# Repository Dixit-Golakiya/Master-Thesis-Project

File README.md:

# Microcontroller-Based Health Monitoring System for Supercapacitors

**Master's Thesis — Hochschule Bremen, Department of Electronics Engineering**
In cooperation with BLOCK Transformatoren-Elektronik GmbH

| | |
|---|---|
| **Author** | Golakiya Dixit |
| **Date** | 06.05.2026 |
| **Examiners** | Prof. Dr.-Ing. Dennis Kampen, Prof. Dr.-Ing. Friedrich Fleischmann |
| **Supervisor** | Dipl.-Ing. Henning Sauerland |

📄 Full thesis report: [`docs/Master_Thesis_5274929_Dixit_Golakiya.pdf`](docs/Master_Thesis_5274929_Dixit_Golakiya.pdf)

---

## Table of Contents

- [Abstract](#abstract)
- [Gallery](#gallery)
- [System Overview](#system-overview)
- [Repository Structure](#repository-structure)
- [Hardware Summary](#hardware-summary)
- [Firmware Summary](#firmware-summary)
- [Build / Open Instructions](#build--open-instructions)
- [Results Snapshot](#results-snapshot)
- [License](#license)
- [Citation](#citation)

---

## Abstract

Supercapacitors are increasingly used in energy storage applications due to their
high power density, rapid charge–discharge capability, and long cycle life. Their
performance degrades over time through capacitance fade and rising equivalent
series resistance (ESR), so monitoring state of health (SoH) is essential for
system efficiency, reliability, and safety.

This project implements a microcontroller-based health monitoring system on an
STM32G474RE platform. The system measures voltage and current during
galvanostatic charge/discharge cycles to estimate per-cell capacitance and ESR
in real time — with no external lab instrumentation. ESR is extracted from the
instantaneous ohmic voltage drop at discharge start, and capacitance from a
least-squares linear regression over the discharge slope. Both run entirely on
the MCU after each discharge cycle, with results reported over UART.

The system was validated on a 40-cell (5 parallel × 8 series) Vishay 25 F
supercapacitor bank, including artificially aged cells (accelerated thermal
ageing), across eleven test configurations. Aged cells were correctly localised
in every tested configuration, with capacitance drops of 10.9–16.5% in
single-string tests and a practical detection floor of ~10% per-cell loss in a
four-string parallel bank.

---

## Gallery

<table>
<tr>
<td width="50%">

<p align="center"><sub><b>Assembled board — isometric view</b></sub></p>
</td>
<td width="50%">

<p align="center"><sub><b>Assembled board — alternate angle</b></sub></p>
</td>
</tr>
<tr>
<td width="50%">

<p align="center"><sub><b>PCB 3D render — top</b></sub></p>
</td>
<td width="50%">

<p align="center"><sub><b>PCB 3D render — bottom</b></sub></p>
</td>
</tr>
<tr>
<td width="50%">

<p align="center"><sub><b>Galvanostatic discharge waveform</b></sub></p>
</td>
<td width="50%">

<p align="center"><sub><b>Least-squares capacitance regression</b></sub></p>
</td>
</tr>
<tr>
<td width="50%">

<p align="center"><sub><b>Power density comparison</b></sub></p>
</td>
<td width="50%">

<p align="center"><sub><b>LTspice discharge model simulation</b></sub></p>
</td>
</tr>
</table>

Higher-resolution schematic renders (front/back copper) are also available as PDFs in
[`Figure/`](Figure/): [`A_Super_Capacitor_measurement.pdf`](Figure/A_Super_Capacitor_measurement.pdf),
[`B_1_Super_Capacitor_measurement-F_Cu.pdf`](Figure/B_1_Super_Capacitor_measurement-F_Cu.pdf),
[`B_2_Super_Capacitor_measurement-B_Cu.pdf`](Figure/B_2_Super_Capacitor_measurement-B_Cu.pdf).

---

## System Overview

```
STM32G4 Nucleo-64 Board
   ├── Voltage Divider Network                  → 8 series-cell node voltages → ADC
   ├── Shunt Current Sensors (INA241A1 × 2)      → analog input
   ├── Hall-Effect Sensor (TMCS1108A3)           → analog input, isolated
   ├── MOSFET Current Sink (IRL540N / FQA140N10) → DAC/PWM controlled
   ├── Threshold Comparators (TLV3541)           → hardware end-of-discharge trigger
   ├── User Buttons (S1–S7) + Status LEDs
   └── UART Interface → external monitor / logging
```

**Key design points:**

- 12-bit ADC with 32× hardware oversampling → ~14.5-bit ENOB, enabling ohmic-drop
  resolution without external instrumentation amplifiers.
- Per-cell (per-node) resolution — a bank-level average alone cannot localise
  which cell is degrading.
- ESR from a 10-sample pre-trigger baseline vs. first post-commutation sample.
- Capacitance from a sliding-window least-squares regression (tiered by R²/RMSE
  quality) over the constant-current discharge slope, from `Vrated` down to
  `0.866 × Vrated` (75% of stored energy).
- Cross-validated current sensing across two INA241A1 shunt amplifiers and one
  isolated Hall-effect sensor.

---

## Repository Structure

```
.
├── README.md
├── LICENSE
├── .gitignore
│
├── docs/
│   └── Master_Thesis_5274929_Dixit_Golakiya.pdf   # Full thesis (Golakiya Dixit, HSB, 2026)
│
├── Figure/                          # Photos, renders, and plots used in this README / thesis
│
├── Hardware/
│   └── KiCad/                       # KiCad 9.0 project — schematics + 2-layer PCB
│       └── README.md
│
├── Simulation/
│   └── LTSpice/                     # LTspice models: divider network, DAC current sink,
│       └── README.md                # first-order ESR/capacitance discharge model
│
├── Firmware/
│   └── STM32/                       # STM32CubeIDE / HAL firmware (FSM-based)
│       └── README.md
│
└── results/                         # Measurement data, plots, validation exports
```

## Hardware Summary

| Component                | Part                                  | Role                                     |
| ------------------------ | -------------------------------------- | ----------------------------------------- |
| MCU                       | STM32G474RE (Nucleo-64)               | ADC/DAC, regression math, FSM control    |
| Supercapacitors           | Vishay 25 F × 40 (5P-8S)              | Bank under test — 24 V, 15.625 F nominal |
| Current sense (shunt)     | INA241A1 × 2                          | High-accuracy discharge/charge current   |
| Current sense (isolated)  | TMCS1108A3                            | Redundant, galvanically isolated         |
| Current sink MOSFET       | IRL540N (TO-220) / FQA140N10 (TO-247) | Galvanostatic discharge load             |
| Comparators                | TLV3541 × 2                          | Hardware end-of-discharge interrupt      |
| PCB                        | KiCad 9.0, 2-layer, 192 mm × 166 mm  | Custom board around Nucleo-64            |

## Firmware Summary

Six-state FSM: **Initialisation → Idle → Pre-trigger Acquisition → Discharge →
Parameter Extraction → Result Transmission**, driven by hardware comparator
interrupts and DMA-buffered ADC acquisition (14 channels across ADC1/ADC2/ADC5,
synchronised via TIM3 at 1 kHz). Written in C using STM32CubeIDE + HAL.

## Build / Open Instructions

- **Hardware:** Open `Hardware/KiCad/*.kicad_pro` in **KiCad 9.0** or later.
- **Simulation:** Open `.asc` files in `Simulation/LTSpice/` with **LTspice
  XVII (v24.1.5)** or later.
- **Firmware:** Import `Firmware/STM32/` as an existing project in
  **STM32CubeIDE**, or regenerate the base code from the included `.ioc` file
  via STM32CubeMX. Flash to a **NUCLEO-G474RE** board.

See the README in each subfolder for details specific to that part.

## Results Snapshot

- Parallel capacitance scaling within **1.1%** of theoretical `Np × Csingle`.
- Regression fit quality: **R² > 0.993** across all tested configurations.
- Aged-cell detection: **0 false positives** across all 11 test configurations.
- Repeatability: capacitance measurements stable to **±0.13 F (1.0%)** across
  9 repeated sessions on the same bank.

Full data, per-configuration plots, and discussion are in Chapter 4 of the
thesis report.

## License

See [`LICENSE`](LICENSE). Choose a license appropriate for your work (e.g. MIT
for firmware/tooling, CERN-OHL for hardware) — update this section once
decided.

## Citation

If referencing this work:

```
Golakiya Dixit, "Development of a Microcontroller-Based Health Monitoring
System for Supercapacitors in Energy Storage Applications," Master's Thesis,
Hochschule Bremen, 2026.
```

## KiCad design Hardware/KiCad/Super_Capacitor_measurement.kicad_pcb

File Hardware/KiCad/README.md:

# Hardware — KiCad Project

Custom 2-layer PCB (192 mm × 166 mm) built around a NUCLEO-G474RE evaluation
board, providing all sensing and excitation circuitry for the supercapacitor
health monitoring system.

## Contents (place your exported KiCad project here)

```
kicad/
├── Super_Capacitor_measurement.kicad_pro
├── Super_Capacitor_measurement.kicad_sch   (3 sheets: power/input, measurement, MCU/comms)
├── Super_Capacitor_measurement.kicad_pcb
├── Super_Capacitor_measurement.kicad_prl
├── gerbers/        # exported fab files (optional, generate before final commit)
├── 3d-renders/     # isometric top/bottom views
└── bom/            # bill of materials (csv/xlsx export)
```

> Commit the whole KiCad project folder as-is — KiCad manages internal file
> relationships (`.kicad_pro`, `.kicad_sch`, `.kicad_pcb`, `.kicad_prl`)
> and cherry-picking files can break the project when reopened.

## Key subsystems (see thesis Ch. 3 for full derivations)

- **Voltage divider network** — 8 series-cell nodes scaled into the
  0–3.3 V ADC range (node 8 direct, no divider needed).
- **Current sensing** — 2× INA241A1 (shunt-based, 20 V/V gain, 33 mΩ shunt)
  + 1× TMCS1108A3 (isolated Hall-effect, 0.2 V/A).
- **Controlled current sink** — DAC-driven IRL540N/FQA140N10 MOSFET,
  closed-loop regulated via a two-comparator (TLV3541) feedback network.
- **Status/UI** — 5 status LEDs, 2 toggle switches (mode select), 5 push
  buttons (S3–S7: emergency stop, start measurement, calibrate, arm passive
  discharge, start galvanostatic discharge).

## Layout notes

- RC filters on ADC inputs and op-amp/Hall sensor supply pins for noise
  rejection.
- Bottom-layer ground plane to reduce EMI coupling into high-impedance
  divider inputs.
- Kelvin connections at both shunt resistors.
- Short ADC input traces to minimise parasitic capacitance/crosstalk.

## Tooling

- **KiCad 9.0** or later.
- 3D renders exported via KiCad's built-in 3D viewer.

## Bill of Materials

See `bom/` for the full BOM export. Key parts: STM32G474RE (Nucleo-64),
Vishay 25 F supercapacitors ×40, INA241A1 ×2, TMCS1108A3, TLV3541 ×2,
IRL540N + FQA140N10 MOSFETs.

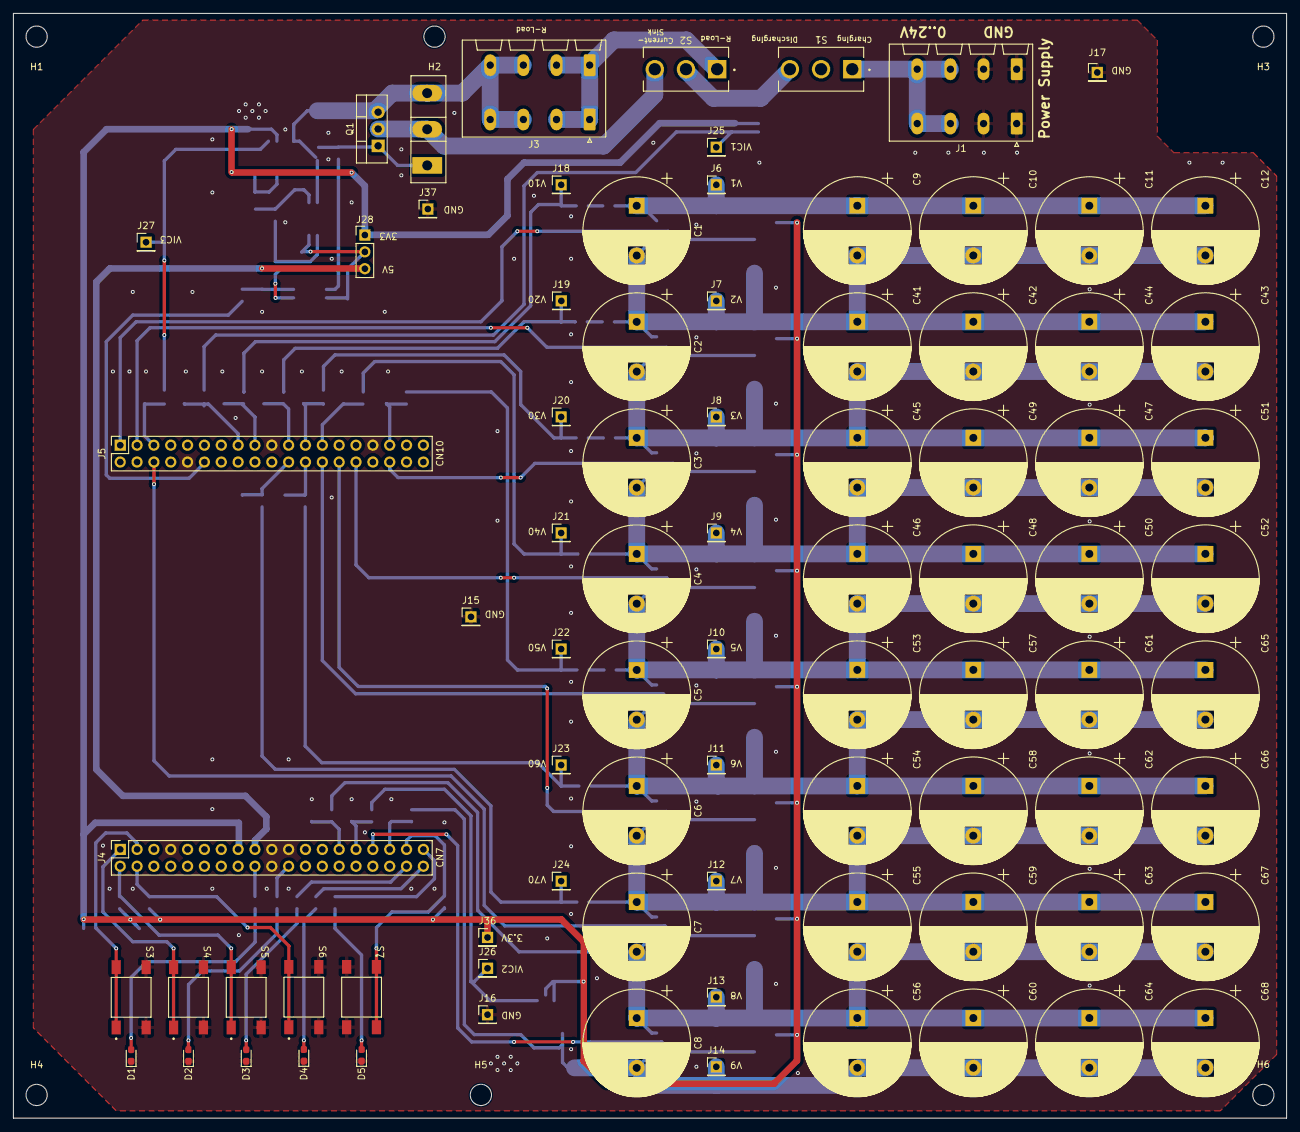
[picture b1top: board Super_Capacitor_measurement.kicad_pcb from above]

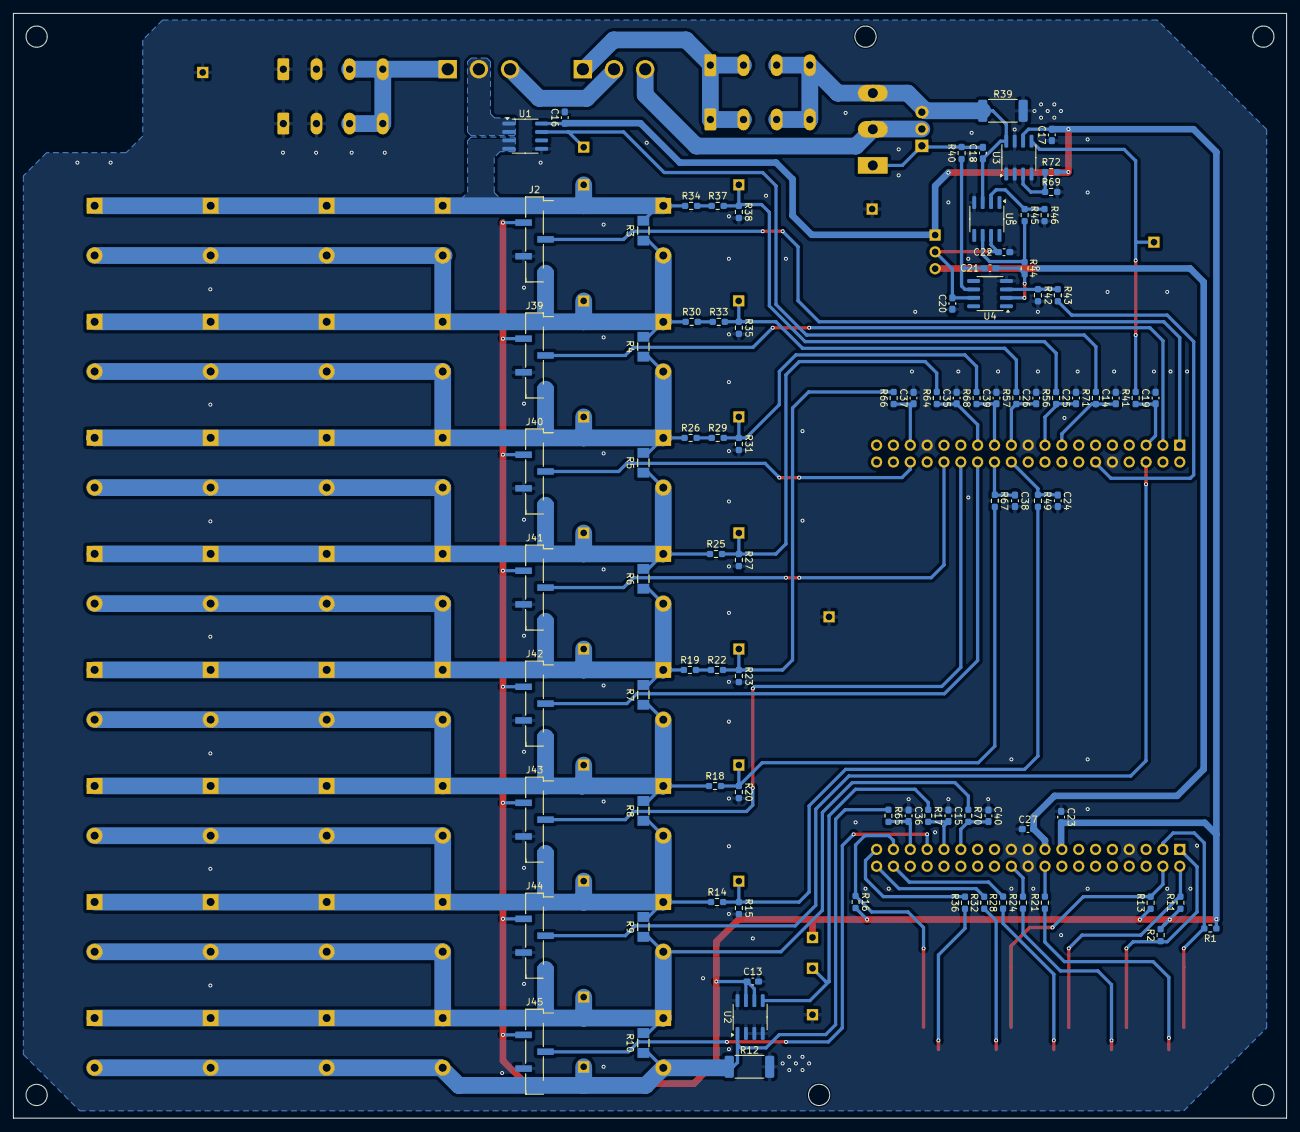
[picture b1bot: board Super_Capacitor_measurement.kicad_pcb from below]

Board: 2 copper layers, 192.0 x 166.6 mm, 181 parts (92 on the bottom side), 76 nets.

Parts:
C1, C2, C3, C4, C5, C6, C7, C8, C9, C10, C11, C12, C41, C42, C43, C44, C45, C46, C47, C48, C49, C50, C51, C52, C53, C54, C55, C56, C57, C58, C59, C60, C61, C62, C63, C64, C65, C66, C67, C68: 25; CP_Radial_D16.0mm_P7.50mm
C13, C14, C15, C16, C17, C18, C19, C20, C21, C22, C23, C24, C25, C26, C27, C35, C36, C37, C38, C39, C40: c=100n; C_0603_1608Metric_Pad1.08x0.95mm_HandSolder
D1, D3: LED-GREEN; LED_0603_1608Metric_Pad1.05x0.95mm_HandSolder
D2, D4: LED-YELLOW; LED_0603_1608Metric_Pad1.05x0.95mm_HandSolder
D5: LED-RED; LED_0603_1608Metric_Pad1.05x0.95mm_HandSolder
H1, H2, H3, H4, H5, H6: MountingHole; MountingHole_3.2mm_M3
J1, J3: PBK 2,5/4/5,00-H GN; PhoenixContact_SPT_2.5_4-H-5.0_1x04_P5.0mm_Horizontal
J2, J39, J40, J41, J42, J43, J44, J45: Conn_01x05_Pin; PinHeader_1x05_P2.54mm_Vertical_SMD_Pin1Right
J4: CN7; PinSocket_2x19_P2.54mm_Vertical
J5: CN10; PinSocket_2x19_P2.54mm_Vertical
J6, J7, J8, J9, J10, J11, J12, J13, J14, J15, J16, J17, J18, J19, J20, J21, J22, J23, J24, J25, J26, J27, J36, J37: Conn_01x01_Pin; PinHeader_1x01_P2.54mm_Vertical
J28: Conn_01x03_Pin; PinHeader_1x03_P2.54mm_Vertical
Q1: IRL540N; TO-220-3_Vertical
Q2: IRL540N; TO-247-3_Vertical
R1, R2, R11, R13, R16: 10k; R_0603_1608Metric_Pad0.98x0.95mm_HandSolder
R3, R4, R5, R6, R7, R8, R9, R10: 510; R_MiniMELF_MMA-0204
R12, R39: 0.033; R_2512_6332Metric_Pad1.40x3.35mm_HandSolder
R14, R15, R20, R23, R26, R27, R31, R35, R38: 75k; R_0603_1608Metric_Pad0.98x0.95mm_HandSolder
R17, R41, R49, R56, R57, R64, R65, R66, R67, R68, R70, R71: 160; R_0603_1608Metric_Pad0.98x0.95mm_HandSolder
R18, R30: 150k; R_0603_1608Metric_Pad0.98x0.95mm_HandSolder
R19: 5k; R_0603_1608Metric_Pad0.98x0.95mm_HandSolder
R21, R24, R28, R32, R36: 620; R_0603_1608Metric_Pad0.98x0.95mm_HandSolder
R22: 220k; R_0603_1608Metric_Pad0.98x0.95mm_HandSolder
R25, R29, R33: 300k; R_0603_1608Metric_Pad0.98x0.95mm_HandSolder
R34: 15k; R_0603_1608Metric_Pad0.98x0.95mm_HandSolder
R37: 510k; R_0603_1608Metric_Pad0.98x0.95mm_HandSolder
R40: 100; R_0603_1608Metric_Pad0.98x0.95mm_HandSolder
R42: 3k; R_0603_1608Metric_Pad0.98x0.95mm_HandSolder
R43: 12k; R_0603_1608Metric_Pad0.98x0.95mm_HandSolder
R44: 470; R_0603_1608Metric_Pad0.98x0.95mm_HandSolder
R45: 9k; R_0603_1608Metric_Pad0.98x0.95mm_HandSolder
R46: 1k; R_0603_1608Metric_Pad0.98x0.95mm_HandSolder
R69, R72: 0; R_0603_1608Metric_Pad0.98x0.95mm_HandSolder
S1, S2: 500SSP1S2M2QEA; SW_500SSP1S2M2QEA
S3, S4, S5, S6, S7: TS04; SW_TS04
U1: TMCS1108A3UQDR; SOIC-8_3.9x4.9mm_P1.27mm
U2, U3: INA241A1xD; SOIC-8_3.9x4.9mm_P1.27mm
U4, U5: TLV3541IDR; SOIC-8_3.9x4.9mm_P1.27mm

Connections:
3V3: C13.1, C16.1, C17.1, C23.1, J2.2, J4.15, J28.1, J36.1, J39.2, J40.2, J41.2, J42.2, J43.2, J44.2, J45.2, R1.2, R2.2, R11.2, R13.2, R16.2, R72.2, U1.8 (VS), U2.6 (V+), U2.7 (REF1), U3.6 (V+)
5V: C27.2, J4.17, J28.3
/PA0: C40.1, J4.27, R70.1
/PA4: J4.31, J45.3
/PA5: J5.12, R43.1
/PA8: C38.2, J5.24, R67.1
/PA9: C24.1, J5.22, R49.1
/PA10: J5.34, J40.3
/PA15: J4.18, R21.2
/PB0: C36.1, J4.33, R65.1
/PB1: C39.1, J5.23, R68.1
/PB2: C26.2, J5.21, R57.1
/PB4: J5.28, J43.3
/PB5: J5.30, J41.3
/PB7: J4.22, R24.2
/PB9: J5.6, J44.3
/PB10: J5.26, J42.3
/PB11: C25.2, J5.17, R56.2
/PB15: C35.1, J5.25, R64.1
/PC0: J4.37, R36.2
/PC1: J4.35, R16.1, S7.1, S7.3
/PC2: J4.36, R28.2
/PC3: J4.38, R32.2
/PC4: C37.2, J5.33, R66.1
/PC6: J5.3, J39.3
/PC8: J2.3, J5.1
/PC10: J4.2, R11.1, S5.1, S5.3
/PC11: J4.1, R2.1, S4.1, S4.3
/PC12: J4.4, R13.1, S6.1, S6.3
/PD2: J4.3, R1.1, S3.1, S3.3
/V1: C1.1, C9.1, C10.1, C11.1, C12.1, J2.1, J6.1, R3.1, R34.1, U1.3 (IN-), U1.4 (IN-)
/V2: C1.2, C2.1, C9.2, C10.2, C11.2, C12.2, C41.1, C42.1, C43.1, C44.1, J2.5, J7.1, J39.1, R3.2, R4.1, R30.1
/V3: C2.2, C3.1, C41.2, C42.2, C43.2, C44.2, C45.1, C47.1, C49.1, C51.1, J8.1, J39.5, J40.1, R4.2, R5.1, R26.1
/V4: C3.2, C4.1, C45.2, C46.1, C47.2, C48.1, C49.2, C50.1, C51.2, C52.1, J9.1, J40.5, J41.1, R5.2, R6.1, R25.1
/V5: C4.2, C5.1, C46.2, C48.2, C50.2, C52.2, C53.1, C57.1, C61.1, C65.1, J10.1, J41.5, J42.1, R6.2, R7.1, R19.2
/V6: C5.2, C6.1, C53.2, C54.1, C57.2, C58.1, C61.2, C62.1, C65.2, C66.1, J11.1, J42.5, J43.1, R7.2, R8.1, R18.1
/V7: C6.2, C7.1, C54.2, C55.1, C58.2, C59.1, C62.2, C63.1, C66.2, C67.1, J12.1, J43.5, J44.1, R8.2, R9.1, R14.1
/V8: C7.2, C8.1, C55.2, C56.1, C59.2, C60.1, C63.2, C64.1, C67.2, C68.1, J13.1, J44.5, J45.1, R9.2, R10.1, R70.2
/V9: C8.2, C56.2, C60.2, C64.2, C68.2, J14.1, J45.5, R10.2, R12.1, R65.2, U2.1 (-)
/V10: J18.1, R37.2, R38.1, R56.1
/V20: J19.1, R33.2, R35.1, R57.2
/V30: J20.1, R29.2, R31.1, R68.2
/V40: J21.1, R25.2, R27.1, R64.2
/V50: J22.1, R22.2, R23.1, R66.2
/V60: J23.1, R18.2, R20.1, R67.2
/V70: J24.1, R14.2, R15.1, R49.2
/VIC1: J25.1, R71.1, U1.7 (VOUT)
/VIC2: J26.1, R17.1, U2.5
/VIC3: J27.1, R41.1, U3.5
GND: C13.2, C14.2, C15.2, C16.2, C17.2, C19.2, C20.2, C22.2, C23.2, C24.2, C25.1, C26.1, C27.1, C35.2, C36.2, C37.1, C38.1, C39.2, C40.2, D1.1, D2.1, D3.1, D4.1, D5.1, J1.1, J1.2, J2.4, J4.7, J4.19, J4.20, J4.21, J5.10, J5.19, J5.31, J15.1, J16.1, J17.1, J37.1, J39.4, J40.4, J41.4, J42.4, J43.4, J44.4, J45.4, R12.2, R15.2, R20.2, R23.2, R27.2, R31.2, R35.2, R38.2, R39.2, R42.1, R46.1, R69.1, S3.2, S3.4, S4.2, S4.4, S5.2, S5.4, S6.2, S6.4, S7.2, S7.4, U1.5 (GND), U2.2 (GND), U2.3 (REF2), U2.4 (GND), U2.8 (+), U3.1 (-), U3.2 (GND), U3.4 (GND), U3.7 (REF1), U4.4 (V-), U5.4 (V-)
IC1: C14.1, J5.15, R71.2
IC2: C15.1, J4.29, R17.2
IC3: C19.1, J5.5, R41.2
unnamed: D1.2, R21.1
unnamed: D2.2, R24.1
unnamed: D3.2, R28.1
unnamed: D4.2, R32.1
unnamed: D5.2, R36.1
unnamed: J1.3, J1.4, S1.1
unnamed: J3.1, J3.2, S2.1
unnamed: C18.2, J3.3, J3.4, Q1.3 (S), Q2.3 (S), R39.1, U3.8 (+), U5.3 (IN+)
unnamed: C20.1, C22.1, J28.2, U4.7 (V+), U5.7 (V+)
unnamed: Q1.2 (D), Q2.2 (D), S2.3
unnamed: C18.1, Q1.1 (G), Q2.1 (G), R40.1
unnamed: R19.1, R22.1
unnamed: R26.2, R29.1
unnamed: R30.2, R33.1
unnamed: R34.2, R37.1
unnamed: S1.2, U1.1 (IN+), U1.2 (IN+)
unnamed: S1.3, S2.2
unnamed: R69.2, R72.1, U3.3 (REF2)
unnamed: R42.2, R43.2, U4.3 (IN+)
unnamed: C21.2, R44.1, U4.2 (IN-)
unnamed: C21.1, R40.2, U4.6 (OUT)
unnamed: R45.2, R46.2, U5.2 (IN-)
unnamed: R44.2, R45.1, U5.6 (OUT)

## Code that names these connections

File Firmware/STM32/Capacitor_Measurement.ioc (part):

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Mcu.Name=STM32G474R(B-C-E)Tx
Mcu.Package=LQFP64
Mcu.UserName=STM32G474RETx
PA0.GPIOParameters=GPIO_Label
PA0.GPIO_Label=V08
PA0.Mode=IN1-Single-Ended
PA0.Signal=ADC1_IN1
PA1.GPIOParameters=GPIO_Label
PA1.GPIO_Label=IC2
PA1.Mode=IN2-Single-Ended
PA1.Signal=ADC1_IN2
PA13.GPIOParameters=GPIO_Label
PA13.GPIO_Label=T_SWDIO
PA13.Mode=Serial_Wire
PA13.Signal=SYS_JTMS-SWDIO
PA14.GPIOParameters=GPIO_Label
PA14.GPIO_Label=T_SWCLK
PA14.Mode=Serial_Wire
PA14.Signal=SYS_JTCK-SWCLK
PA15.GPIOParameters=GPIO_Label
PA15.GPIO_Label=LD1
PA15.Signal=GPIO_Output
PA2.Mode=Asynchronous
PA2.Signal=USART2_TX
PA5.Signal=COMP_DAC12_group
PA8.GPIOParameters=GPIO_Label
PA8.GPIO_Label=V60
PA8.Mode=IN1-Single-Ended
PA8.Signal=ADC5_IN1
PA9.GPIOParameters=GPIO_Label
PA9.GPIO_Label=V70
PA9.Mode=IN2-Single-Ended
PA9.Signal=ADC5_IN2
PB0.GPIOParameters=GPIO_Label
PB0.GPIO_Label=V09
PB0.Mode=IN15-Single-Ended
PB0.Signal=ADC1_IN15
PB1.GPIOParameters=GPIO_Label
PB1.GPIO_Label=V30
PB1.Mode=IN12-Single-Ended
PB1.Signal=ADC1_IN12
PB11.GPIOParameters=GPIO_Label
PB11.GPIO_Label=V10
PB11.Mode=IN14-Single-Ended
PB11.Signal=ADC1_IN14
PB12.GPIOParameters=GPIO_Label
PB12.GPIO_Label=IC1
PB12.Mode=IN11-Single-Ended
PB12.Signal=ADC1_IN11
PB15.GPIOParameters=GPIO_Label
PB15.GPIO_Label=V40
PB15.Mode=IN15-Single-Ended
PB15.Signal=ADC2_IN15
PB2.GPIOParameters=GPIO_Label
PB2.GPIO_Label=V20
PB2.Mode=IN12-Single-Ended
PB2.Signal=ADC2_IN12
PB3.GPIOParameters=GPIO_Label
PB3.GPIO_Label=T_SWO
PB3.Signal=SYS_JTDO-SWO
PB4.Mode=Asynchronous
PB4.Signal=USART2_RX
PB7.GPIOParameters=GPIO_Label,GPIO_FM7
PB7.GPIO_FM7=__NULL
PB7.GPIO_Label=LD2
PB7.Signal=GPIO_Output
PC0.GPIOParameters=GPIO_Label
PC0.GPIO_Label=LD5
PC0.Signal=GPIO_Output
PC1.GPIOParameters=GPIO_PuPd,GPIO_Label,GPIO_ModeDefaultEXTI
PC1.GPIO_Label=S5
PC1.GPIO_ModeDefaultEXTI=GPIO_MODE_IT_FALLING
PC1.GPIO_PuPd=GPIO_PULLUP
PC1.Signal=GPXTI1
PC10.GPIOParameters=GPIO_Label
PC10.GPIO_Label=S3
PC10.Signal=GPXTI10
PC11.GPIOParameters=GPIO_PuPd,GPIO_Label,GPIO_ModeDefaultEXTI
PC11.GPIO_Label=S2
PC11.GPIO_ModeDefaultEXTI=GPIO_MODE_IT_FALLING
PC11.GPIO_PuPd=GPIO_PULLUP
PC11.Signal=GPXTI11
PC12.GPIOParameters=GPIO_PuPd,GPIO_Label,GPIO_ModeDefaultEXTI
PC12.GPIO_Label=S4
PC12.GPIO_ModeDefaultEXTI=GPIO_MODE_IT_FALLING
PC12.GPIO_PuPd=GPIO_PULLUP
PC12.Signal=GPXTI12
PC2.GPIOParameters=GPIO_Label
PC2.GPIO_Label=LD3
PC2.Signal=GPIO_Output
PC3.GPIOParameters=GPIO_Label
PC3.GPIO_Label=LD4
PC3.Signal=GPIO_Output
PC4.GPIOParameters=GPIO_Label
PC4.GPIO_Label=V50
PC4.Mode=IN5-Single-Ended
PC4.Signal=ADC2_IN5
PC5.GPIOParameters=GPIO_Label
PC5.GPIO_Label=IC3
PC5.Mode=IN11-Single-Ended
PC5.Signal=ADC2_IN11
PD2.GPIOParameters=GPIO_PuPd,GPIO_Label,GPIO_ModeDefaultEXTI
PD2.GPIO_Label=S1
PD2.GPIO_ModeDefaultEXTI=GPIO_MODE_IT_FALLING
PD2.GPIO_PuPd=GPIO_PULLUP
PD2.Signal=GPXTI2
RCC.HSE_VALUE=24000000
RCC.SYSCLKFreq_VALUE=16000000
board=NUCLEO-G474RE
boardIOC=true

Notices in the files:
README.md:
License: TBD
